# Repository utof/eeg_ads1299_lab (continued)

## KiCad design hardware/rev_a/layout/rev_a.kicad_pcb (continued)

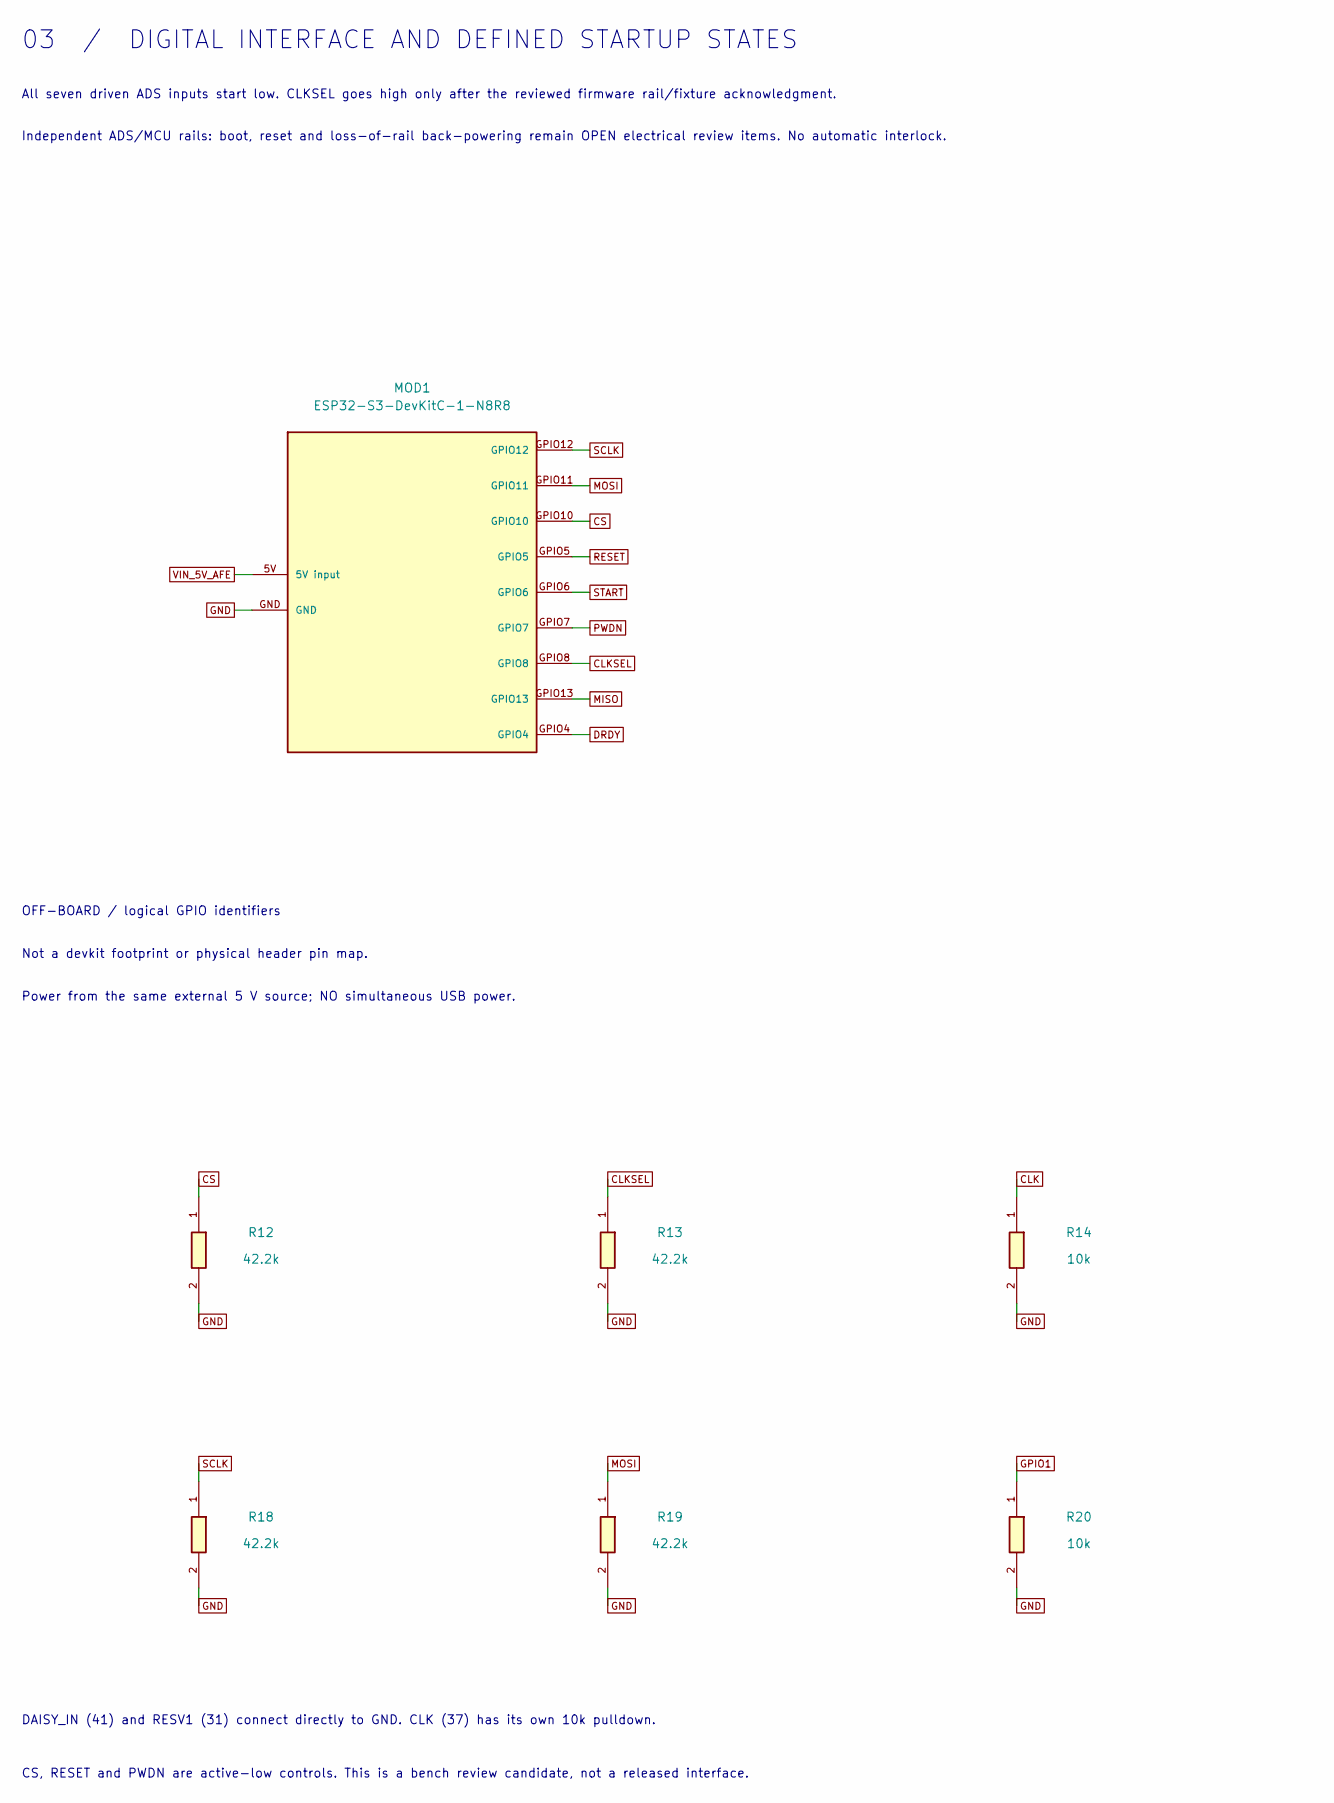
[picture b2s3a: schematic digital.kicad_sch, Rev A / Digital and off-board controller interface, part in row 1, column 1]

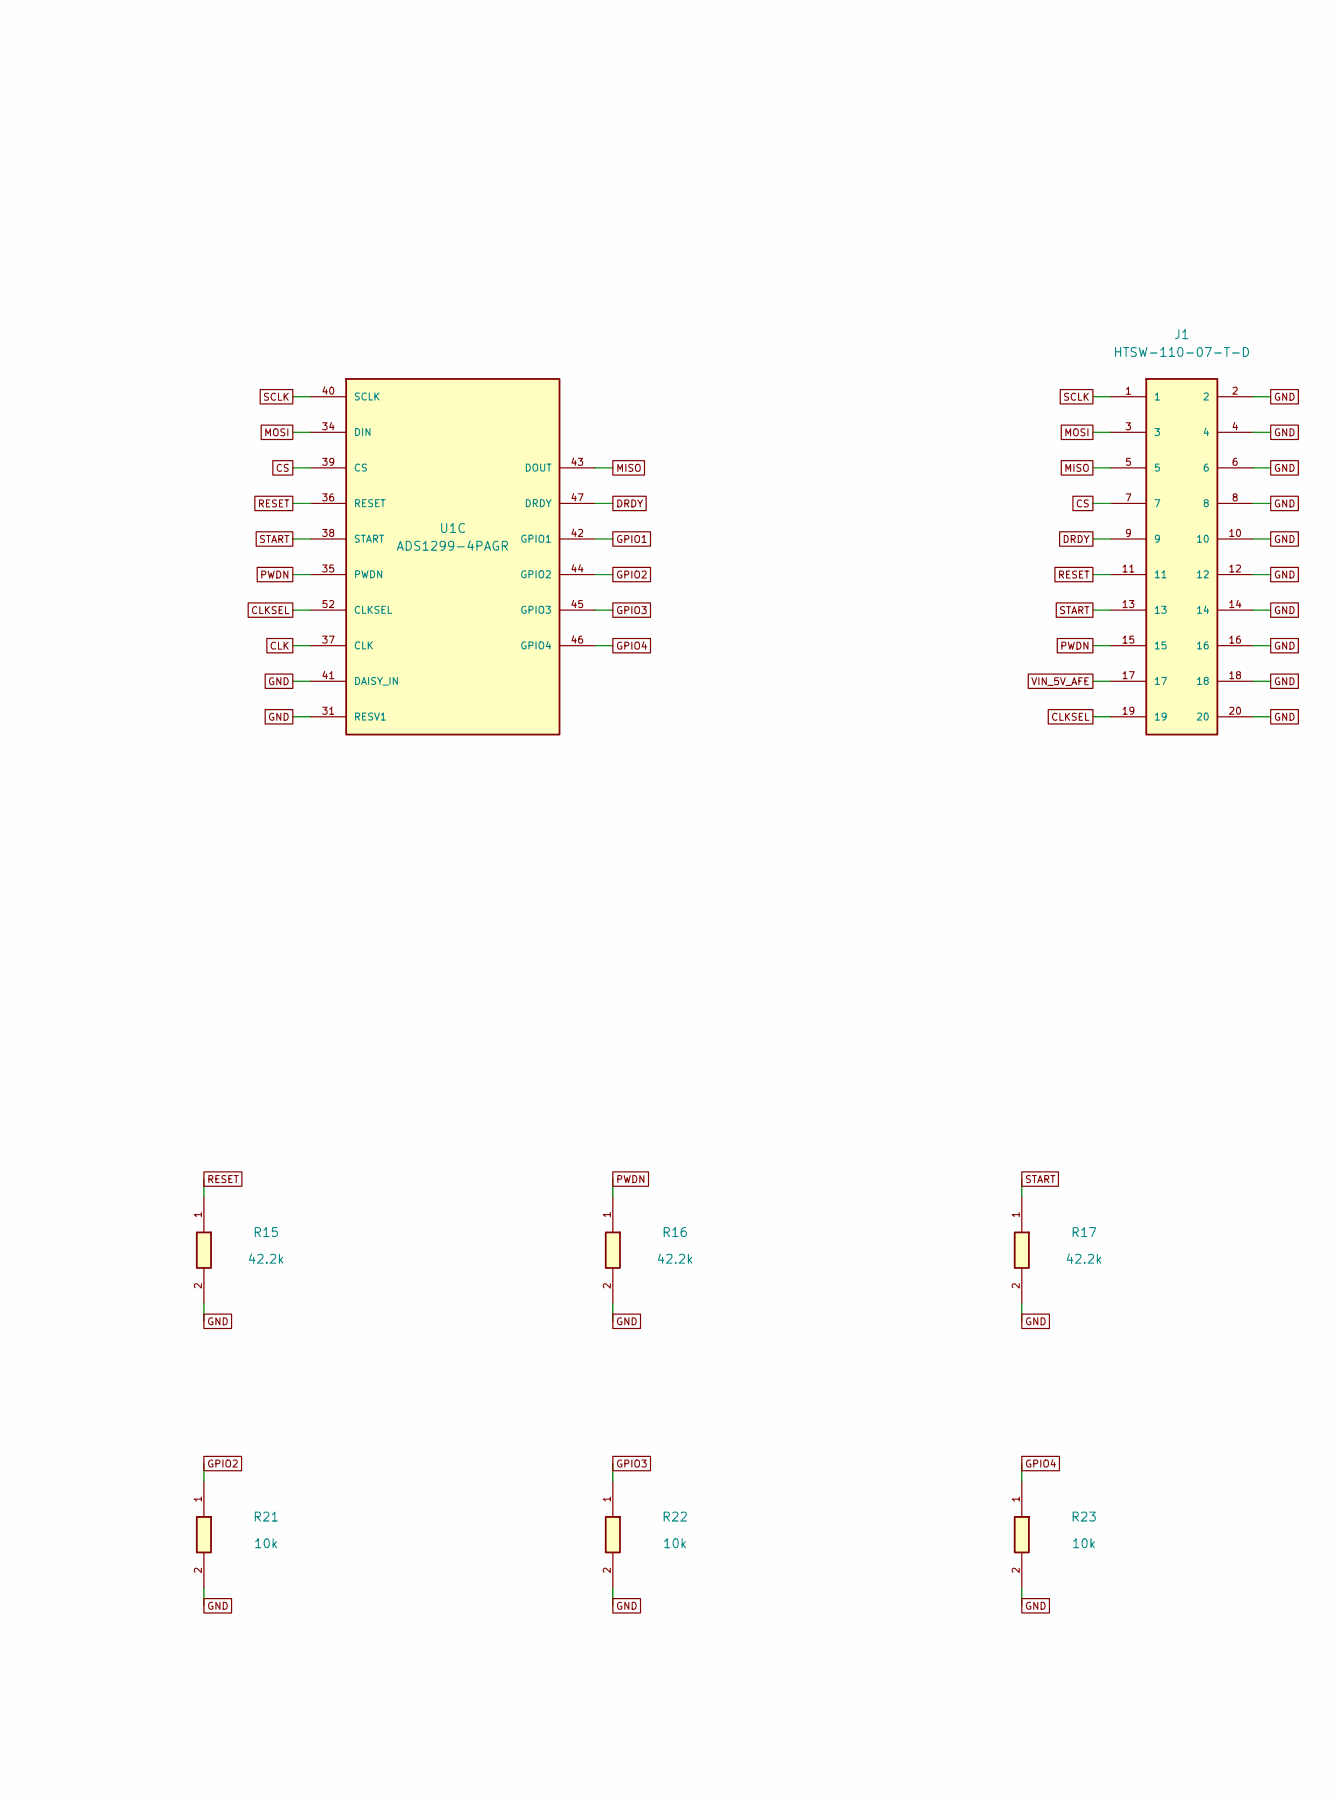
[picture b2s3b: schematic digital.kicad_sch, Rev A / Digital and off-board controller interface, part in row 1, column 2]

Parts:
J1: HTSW-110-07-T-D; PinHeader_2x10_P2.54mm_Vertical; MPN HTSW-110-07-T-D
MOD1: ESP32-S3-DevKitC-1-N8R8; MPN ESP32-S3-DevKitC-1-N8R8
R12, R13, R15, R16, R17, R18, R19: 42.2k; R_0603_1608Metric; Tolerance 0.01; MPN RC0603FR-0742K2L
R14, R20, R21, R22, R23: 10k; R_0603_1608Metric; Tolerance 0.01; MPN RC0603FR-0710KL
U1: ADS1299-4PAGR; TQFP-64_10x10mm_P0.5mm; MPN ADS1299-4PAGR

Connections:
CLK: R14.1, U1.37 (CLK)
CLKSEL: J1.19, MOD1.GPIO8, R13.1, U1.52 (CLKSEL)
CS: J1.7, MOD1.GPIO10, R12.1, U1.39 (CS)
DRDY: J1.9, MOD1.GPIO4, U1.47 (DRDY)
GND: J1.2, J1.4, J1.6, J1.8, J1.10, J1.12, J1.14, J1.16, J1.18, J1.20, MOD1.GND, R12.2, R13.2, R14.2, R15.2, R16.2, R17.2, R18.2, R19.2, R20.2, R21.2, R22.2, R23.2, U1.31 (RESV1), U1.41 (DAISY_IN); also elsewhere on the board
GPIO1: R20.1, U1.42 (GPIO1)
GPIO2: R21.1, U1.44 (GPIO2)
GPIO3: R22.1, U1.45 (GPIO3)
GPIO4: R23.1, U1.46 (GPIO4)
MOSI: J1.3, MOD1.GPIO11, R19.1, U1.34 (DIN)
PWDN: J1.15, MOD1.GPIO7, R16.1, U1.35 (PWDN)
RESET: J1.11, MOD1.GPIO5, R15.1, U1.36 (RESET)
SCLK: J1.1, MOD1.GPIO12, R18.1, U1.40 (SCLK)
START: J1.13, MOD1.GPIO6, R17.1, U1.38 (START)
VIN_5V_AFE: J1.17, MOD1.5V (5V input); also elsewhere on the board

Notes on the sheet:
03 / DIGITAL INTERFACE AND DEFINED STARTUP STATES
All seven driven ADS inputs start low. CLKSEL goes high only after the reviewed firmware rail/fixture acknowledgment.
Independent ADS/MCU rails: boot, reset and loss-of-rail back-powering remain OPEN electrical review items. No automatic interlock.
OFF-BOARD / logical GPIO identifiers
Not a devkit footprint or physical header pin map.
Power from the same external 5 V source; NO simultaneous USB power.
DAISY_IN (41) and RESV1 (31) connect directly to GND. CLK (37) has its own 10k pulldown.
CS, RESET and PWDN are active-low controls. This is a bench review candidate, not a released interface.

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
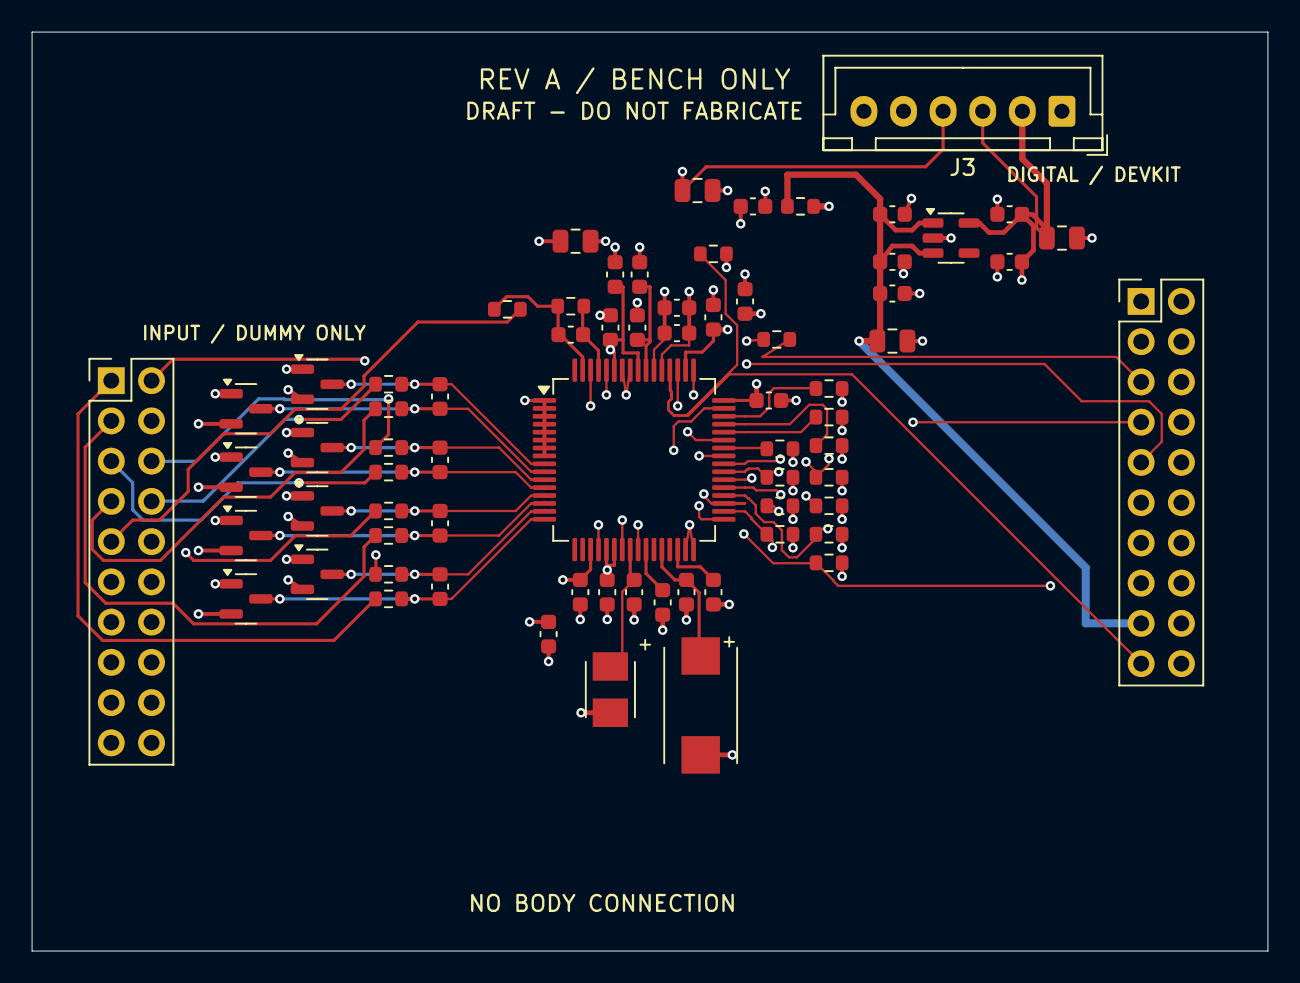
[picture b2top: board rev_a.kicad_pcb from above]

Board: 4 copper layers, 78.0 x 58.0 mm, 70 parts (0 on the bottom side), 43 nets.

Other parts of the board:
R24: NOT_SELECTED; R_0603_1608Metric

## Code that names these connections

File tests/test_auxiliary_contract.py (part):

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        "MCU_3V3",
    ]
    # Gating ARM with READY would manufacture a new rising edge on rail recovery.
    assert parts["ARM_BUFFER"].pins["6"].net == "MCU_3V3"
    assert parts["ARM_BUFFER"].pins["3"].net == "ARM_REQ"
    assert parts["CLEAR_AND"].pins["6"].net == "RAILS_OK"
    assert parts["CLEAR_AND"].pins["3"].net == "SESSION"
    assert parts["MON_D"].pins["1"].net == "AFE_DVDD_SENSE"
    assert parts["MON_A"].pins["1"].net == "AFE_AVDD_SENSE"
    for ref in ("MON_M", "MON_D", "MON_A", "MON_V"):
        assert parts[ref].pins["2"].net == "MCU_3V3"
        assert parts[ref].pins["4"].net == "RAILS_OK"
    assert parts["AFE_RAIL_ACCESS"].pins["2"].net == "AFE_DVDD"
    assert parts["AFE_RAIL_ACCESS"].pins["3"].net == "AFE_DVDD_SENSE"
    assert parts["AFE_TAILS"].pins["19"].net == "AFE_CLKSEL"
    assert all(parts["AFE_TAILS"].pins[str(i)].net == "TARGET_GND" for i in range(2, 21, 2))


def test_every_single_terminal_move_is_detected_by_native_graph_contract() -> None:
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
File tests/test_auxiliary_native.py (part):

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        for path in cad.glob("*.kicad_sch"):
            path.write_text(
                path.read_text().replace(
                    '(global_label "MCU_3V3"', '(global_label "LOGIC_SUPPLY_RENAMED"'
                )
            )
    else:
        _label(cad, "auxiliary", "C101", 1, "HOST_GND")
        _label(cad, "auxiliary", "C101", 2, "HOST_3V3")
    _erc(cad, tmp_path)
    graph = parse_schematic_xml(_export(cad, tmp_path))
    assert (
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    """Real ERC can be made silent by project policy; hashing it is not validation."""
    cad = tmp_path / "cad"
    shutil.copytree(CAD, cad)
    _label(cad, "auxiliary", "U101", 2, "HOST_TX")
    cli = shutil.which("kicad-cli")
    assert cli is not None
    libraries = os.environ.get("KICAD9_FOOTPRINT_DIR")
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
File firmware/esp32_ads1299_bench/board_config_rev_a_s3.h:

#pragma once
// Proposed Rev A digital GPIO map only. No wiring, power or human-use approval.
#if !defined(CONFIG_IDF_TARGET_ESP32S3)
#error "EEGLAB_REV_A_S3 requires CONFIG_IDF_TARGET_ESP32S3."
#endif
constexpr int PIN_SCLK = 12;
constexpr int PIN_MISO = 13;
constexpr int PIN_MOSI = 11;
constexpr int PIN_CS = 10;
constexpr int PIN_DRDY = 4;
constexpr int PIN_RESET = 5;
constexpr int PIN_START = 6;
constexpr int PIN_PWDN = 7;
constexpr int PIN_CLKSEL = 8;
constexpr int EXPECTED_ADS_CHANNELS = 4;

#include "bench_console.h"
